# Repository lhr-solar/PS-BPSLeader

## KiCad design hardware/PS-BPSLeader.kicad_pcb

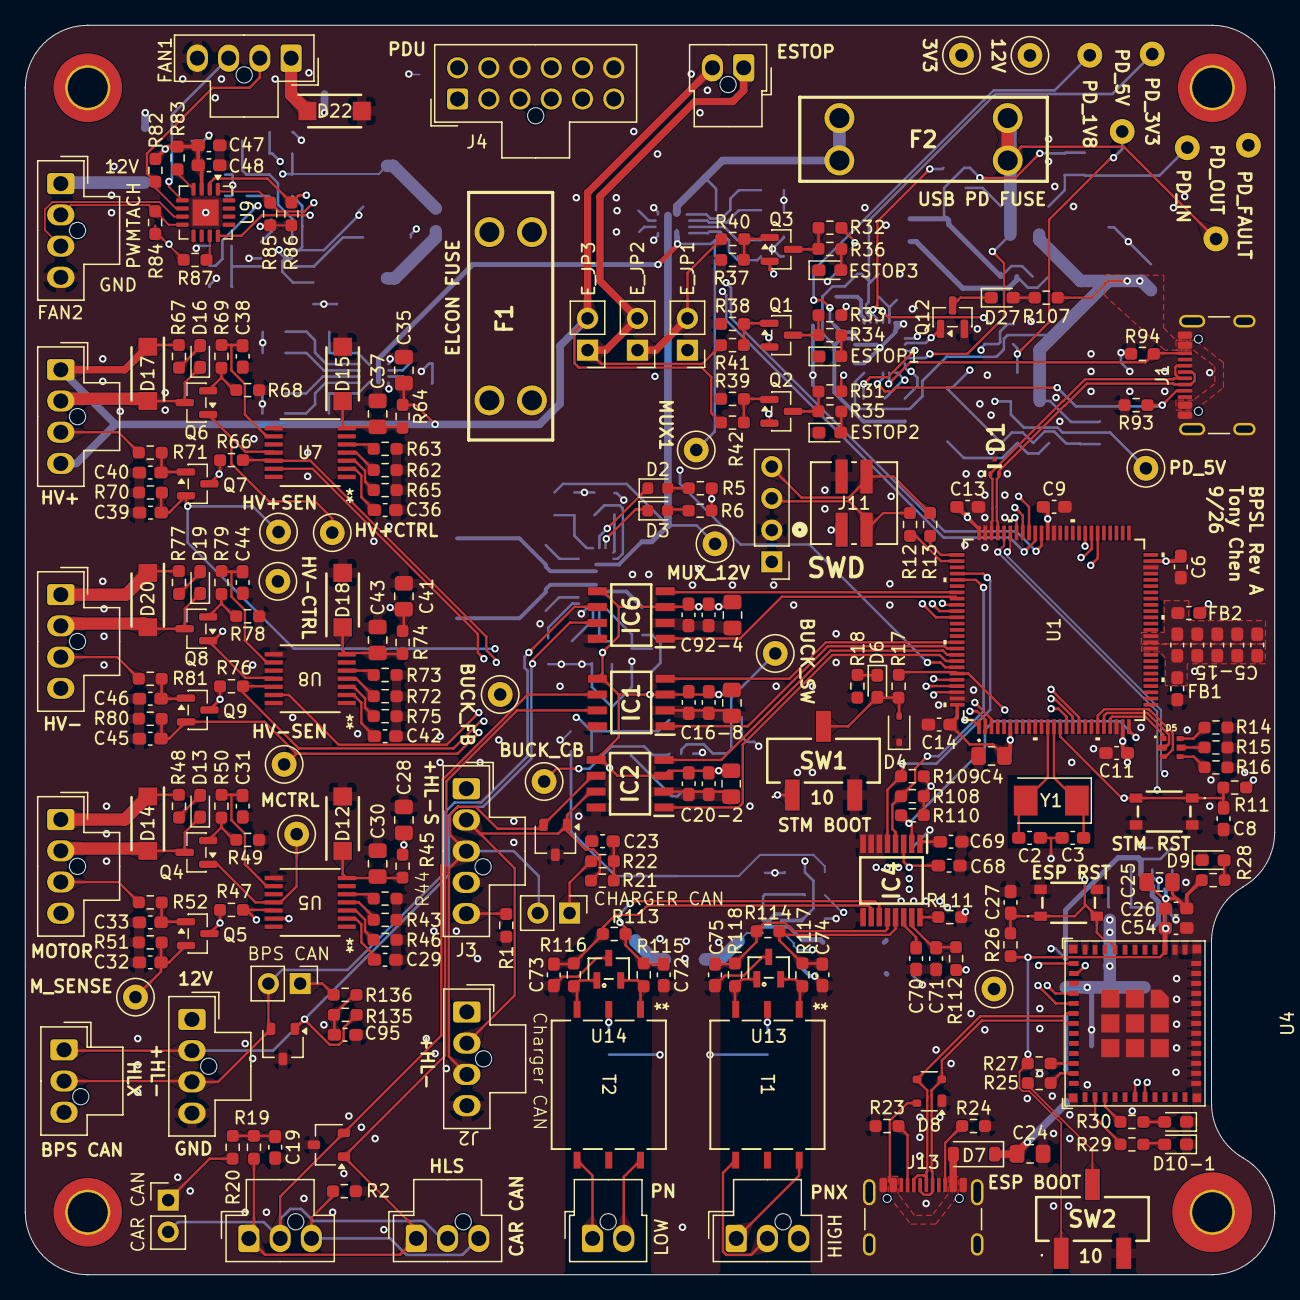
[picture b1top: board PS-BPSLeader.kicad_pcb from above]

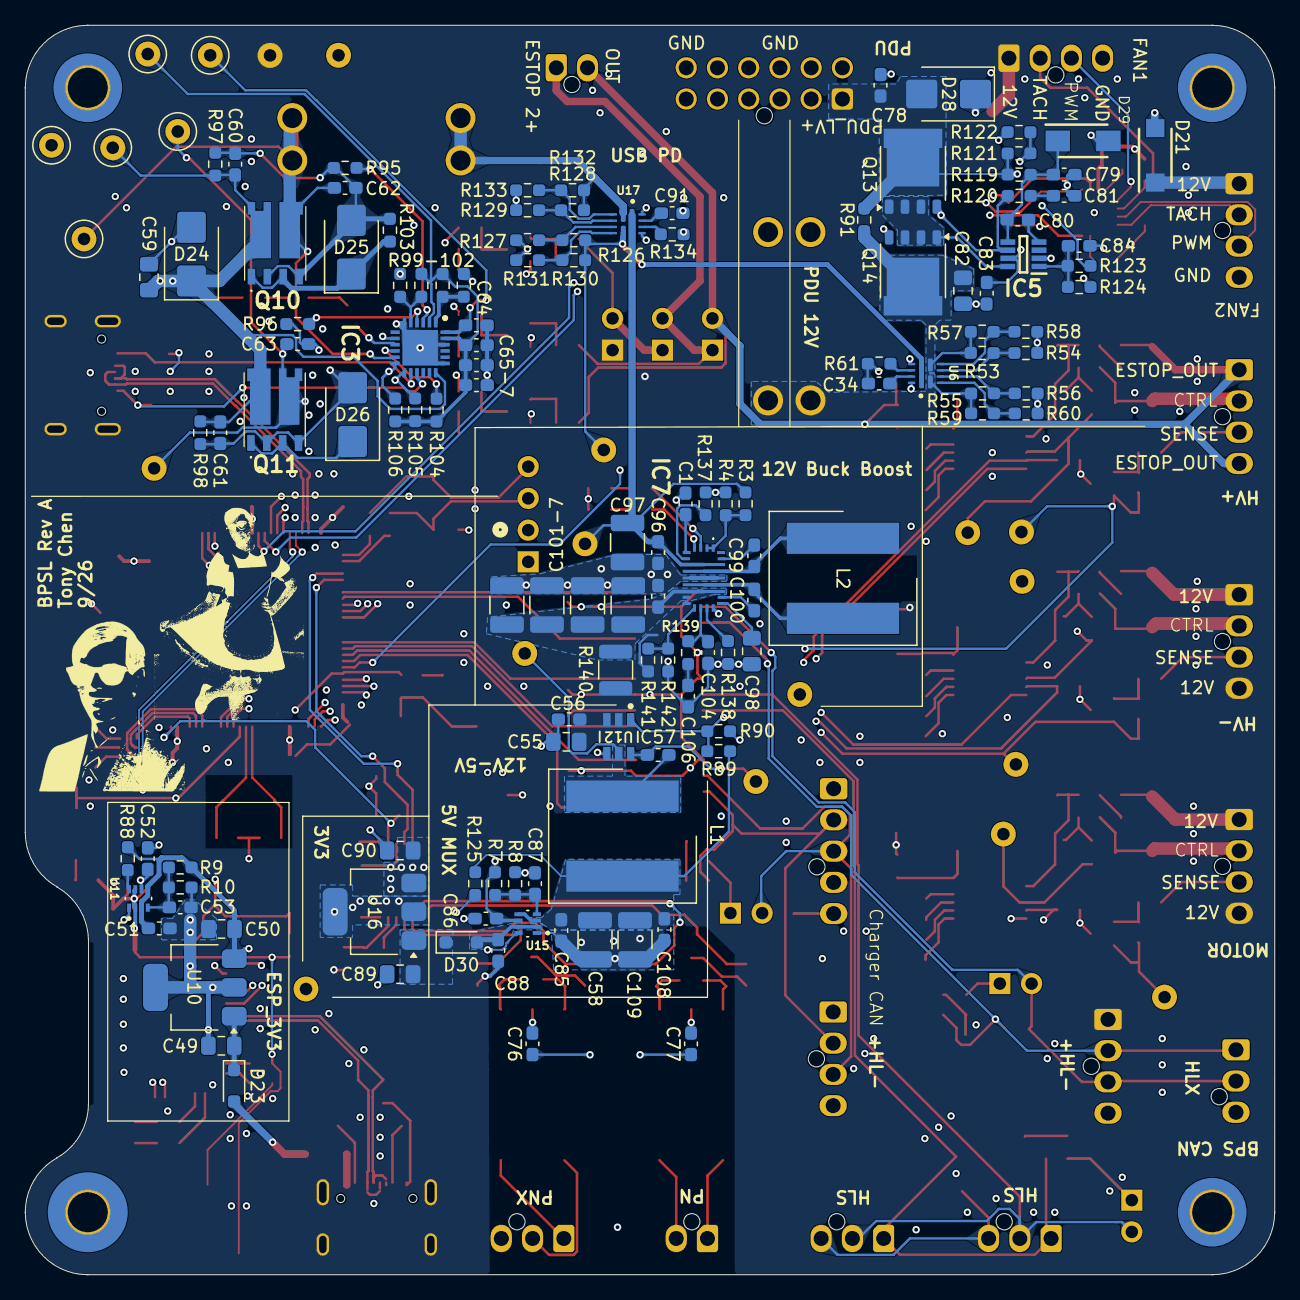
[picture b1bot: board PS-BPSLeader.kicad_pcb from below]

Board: 4 copper layers, 100.0 x 100.0 mm, 387 parts (134 on the bottom side), 230 nets.

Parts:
C1: 7.5n; C_0603_1608Metric_Pad1.08x0.95mm_HandSolder
C2, C3: 26p; C_0603_1608Metric_Pad1.08x0.95mm_HandSolder
C4, C16, C20, C49, C50, C82, C89, C90, C92: 10u; C_0805_2012Metric_Pad1.18x1.45mm_HandSolder
C5, C6, C7, C8, C9, C11, C13, C14, C15, C17, C18, C19, C21, C22, C23, C33, C40, C46, C68, C71, C78, C83, C84, C93, C94, C95, C96, C99, C100, C107: 0.1u; C_0603_1608Metric_Pad1.08x0.95mm_HandSolder
C10, C12, C29, C32, C34, C36, C39, C42, C45, C47, C48, C79, C91: 1u; C_0603_1608Metric_Pad1.08x0.95mm_HandSolder
C24, C25, C59: 10uF; C_0805_2012Metric_Pad1.18x1.45mm_HandSolder
C26, C27, C51, C52, C53, C54, C66, C67, C85, C86, C87, C88: 0.1uF; C_0603_1608Metric_Pad1.08x0.95mm_HandSolder
C28, C30, C35, C37, C41, C43, C55, C98: 4.7u; C_0805_2012Metric_Pad1.18x1.45mm_HandSolder
C31, C38, C44: 0.1n; C_0603_1608Metric_Pad1.08x0.95mm_HandSolder
C56, C57: 100n; C_0603_1608Metric_Pad1.08x0.95mm_HandSolder
C58, C97, C101, C102, C103, C105, C109: 22u; C_1210_3225Metric_Pad1.33x2.70mm_HandSolder
C60, C61, C62, C63, C64, C65: 1uF; C_0603_1608Metric_Pad1.08x0.95mm_HandSolder
C69, C70: 0.22u; C_0603_1608Metric_Pad1.08x0.95mm_HandSolder
C72, C73, C74, C75, C76, C77: 100pF; C_0603_1608Metric_Pad1.08x0.95mm_HandSolder
C80: 220n; C_0603_1608Metric_Pad1.08x0.95mm_HandSolder
C81: 10n; C_0603_1608Metric_Pad1.08x0.95mm_HandSolder
C104: 45p; C_0603_1608Metric_Pad1.08x0.95mm_HandSolder
C106: 90n; C_0603_1608Metric_Pad1.08x0.95mm_HandSolder
C108: 4.7u; C_0603_1608Metric_Pad1.08x0.95mm_HandSolder
D1: TPD2EUSB30DRTR
D2, D3: LED; LED_0603_1608Metric
D4: TVS; D_SOD-323
D5: RGB_LED
D6: LED; LED_0603_1608Metric_Pad1.05x0.95mm_HandSolder
D7: 1N5819HW-7-F; D_SOD-123
D8: SP0503BAHT; SOT-143
D9: ESP_PWR; LED_0603_1608Metric_Pad1.05x0.95mm_HandSolder
D10: ESP_LED1; LED_0603_1608Metric_Pad1.05x0.95mm_HandSolder
D11: ESP_LED2; LED_0603_1608Metric_Pad1.05x0.95mm_HandSolder
D12, D14, D15, D17, D18, D20, D21, D22: VSSAF522-M3/H; SODFL5226X100N
D13, D16, D19: Contact; LED_0603_1608Metric_Pad1.05x0.95mm_HandSolder
D23, D30: SBA130CH-AU_R1_000A1; D_SOD-323_HandSoldering
D24: SMBJ24A-E3_52; D_SMB
D25, D26: SMBJ10A-E3_52; D_SMB
D27: FAULT; LED_0603_1608Metric_Pad1.05x0.95mm_HandSolder
D28: SMBJ15CA; D_SMB
D29: SMAF4758A; SODFL5026X125N
ESTOP1, ESTOP2, ESTOP3: LED; LED_0603_1608Metric_Pad1.05x0.95mm_HandSolder
E_JP1, E_JP2, E_JP3: Jumper_2_Open; PinHeader_1x02_P2.54mm_Vertical
F1, F2: 5A; Fuse-3557-2
FAN1, FAN2: Conn_01x04; Molex_Nano-Fit_105309-xx04_1x04_P2.50mm_Vertical
FB1, FB2: FerriteBead; L_0603_1608Metric_Pad1.05x0.95mm_HandSolder
H1: MountingHole_Pad; MountingHole_3.2mm_M3_Pad_TopBottom
H2, H3, H4: MountingHole_Pad; MountingHole_3.2mm_M3_ISO14580_Pad_TopBottom
IC1, IC2, IC6: TCAN3413DR
IC3: CYPD3177-24LQXQ
IC4: BQ79600PWRQ1; SOP65P640X120-16N
IC5: LM74502DDFR
IC7: TPS552872RYQR; TPS552892QWRYQRQ1
J1, J13: USB_C_Receptacle_USB2.0_16P; USB_C_Receptacle_GCT_USB4105-xx-A_16P_TopMnt_Horizontal
J2: ELCON CAN DEBUG; Molex_Nano-Fit_105309-xx04_1x04_P2.50mm_Vertical
J3: ELCON CAN; Molex_Nano-Fit_105309-xx05_1x05_P2.50mm_Vertical
J4: Conn_02x06_Counter_Clockwise; Molex_Nano-Fit_105310-xx12_2x06_P2.50mm_Vertical
J5: CAR CAN IN; Molex_Nano-Fit_105309-xx03_1x03_P2.50mm_Vertical
J6: CAR CAN OUT; Molex_Nano-Fit_105309-xx03_1x03_P2.50mm_Vertical
J7: BPS CAN DEBUG; Molex_Nano-Fit_105309-xx04_1x04_P2.50mm_Vertical
J8: BPS CAN; Molex_Nano-Fit_105309-xx03_1x03_P2.50mm_Vertical
J9: High Side Conn; Molex_Nano-Fit_105309-xx03_1x03_P2.50mm_Vertical
J10: Low SIde Conn; Molex_Nano-Fit_105309-xx02_1x02_P2.50mm_Vertical
J11: SWD_Header; SWD_Conn
J12: SWD; PinHeader_1x04_P2.54mm_Vertical
J14: Conn_01x02; Molex_Nano-Fit_105309-xx02_1x02_P2.50mm_Vertical
J15, J16, J17: Contactor Connector; Molex_Nano-Fit_105309-xx04_1x04_P2.50mm_Vertical
JP1, JP2, JP3: TRM; PinHeader_1x02_P2.54mm_Vertical
L1: 8.2u; 74439369082
L2: 4.7u; 74439369082
LOGO1: Dr. Hallock; LHRs_LOGO
LOGO2: Dr. Hallock; Hallock_Image_Tiny
Q1, Q2, Q3: SQ2315CES-T1_GE3; SOT-23
Q4, Q5, Q6, Q7, Q8, Q9, Q12: IRLML0030; SOT-23
Q10, Q11: SI7997DP-T1-GE3
Q13, Q14: PSMN012-100YS; LFPAK56
R1, R2, R44, R63, R73, R91: 0; R_0603_1608Metric_Pad0.98x0.95mm_HandSolder
R3: 30.1k; R_0603_1608Metric_Pad0.98x0.95mm_HandSolder
R4, R54, R56, R58, R60, R127, R129, R131, R133: 5k; R_0603_1608Metric_Pad0.98x0.95mm_HandSolder
R5, R6, R14, R15, R16, R18, R28, R29, R30, R34, R35, R36, R45, R50, R64, R69, R74, R79, R95, R96, R101, R113, R114: 1k; R_0603_1608Metric_Pad0.98x0.95mm_HandSolder
R7: 16k; R_0603_1608Metric_Pad0.98x0.95mm_HandSolder
R8, R104: 4.7k; R_0603_1608Metric_Pad0.98x0.95mm_HandSolder
R9: 18k; R_0603_1608Metric_Pad0.98x0.95mm_HandSolder
R10, R11, R17, R25, R26, R27, R31, R32, R33, R37, R38, R39, R47, R51, R52, R66, R70, R71, R76, R80, R81, R82, R84, R85, R86, R88, R97, R107, R108, R109, R119, R125: 10k; R_0603_1608Metric_Pad0.98x0.95mm_HandSolder
R12, R13: 22; R_0603_1608Metric_Pad0.98x0.95mm_HandSolder
R19, R20, R21, R22, R135, R136: 60; R_0603_1608Metric_Pad0.98x0.95mm_HandSolder
R23, R24, R93, R94, R99, R100, R102: 5.1k; R_0603_1608Metric_Pad0.98x0.95mm_HandSolder
R40, R41, R42, R83, R87: 33k; R_0603_1608Metric_Pad0.98x0.95mm_HandSolder
R43, R62, R72: 66.67k; R_0603_1608Metric_Pad0.98x0.95mm_HandSolder
R46, R65, R75: 120k; R_0603_1608Metric_Pad0.98x0.95mm_HandSolder
R48, R67, R77: 4.3k; R_0603_1608Metric_Pad0.98x0.95mm_HandSolder
R49, R68, R78: 1; R_0603_1608Metric_Pad0.98x0.95mm_HandSolder
R53, R126, R132: 57.6k; R_0603_1608Metric_Pad0.98x0.95mm_HandSolder
R55: 67.3k; R_0603_1608Metric_Pad0.98x0.95mm_HandSolder
R57, R130: 26.1k; R_0603_1608Metric_Pad0.98x0.95mm_HandSolder
R59: 37.4k; R_0603_1608Metric_Pad0.98x0.95mm_HandSolder
R61, R134: 22.1k; R_0603_1608Metric_Pad0.98x0.95mm_HandSolder
R89, R110, R111, R121, R123, R128, R141: 100k; R_0603_1608Metric_Pad0.98x0.95mm_HandSolder
R90: 19.1k; R_0603_1608Metric_Pad0.98x0.95mm_HandSolder
R98, R103: 49.9k; R_0603_1608Metric_Pad0.98x0.95mm_HandSolder
R105, R106: 2.2k; R_0603_1608Metric_Pad0.98x0.95mm_HandSolder
R112: 10; R_0603_1608Metric_Pad0.98x0.95mm_HandSolder
R115, R116, R117, R118: 51; R_0603_1608Metric_Pad0.98x0.95mm_HandSolder
R120: 33; R_0603_1608Metric_Pad0.98x0.95mm_HandSolder
R122: 7.32k; R_0603_1608Metric_Pad0.98x0.95mm_HandSolder
R124: 15.8k; R_0603_1608Metric_Pad0.98x0.95mm_HandSolder
R137: 50k; R_0603_1608Metric_Pad0.98x0.95mm_HandSolder
R138: R_US; R_0603_1608Metric_Pad0.98x0.95mm_HandSolder
R139: 1.455k; R_0603_1608Metric_Pad0.98x0.95mm_HandSolder
R140: 12.5m; R_1210_3225Metric
R142: 11.1k; R_0603_1608Metric_Pad0.98x0.95mm_HandSolder
Reset1: Reset; TL3365AF180QG
SW1: SW_SPDT; BootSW
SW2: BOOT Switch; BootSW
SW3: RESET Button; TL3365AF180QG
T1, T2: HMU1228NL; HMU1228NL_PUL
TP1: PD_5V; TestPoint_Loop_D1.80mm_Drill1.0mm_Beaded
TP3: PDU_ELCON; TestPoint_Loop_D1.80mm_Drill1.0mm_Beaded
TP4: MUX_12V; TestPoint_Loop_D1.80mm_Drill1.0mm_Beaded
TP5, TP7, TP9: ctrl; TestPoint_Loop_D1.80mm_Drill1.0mm_Beaded
TP6, TP8, TP10: Sense; TestPoint_Loop_D1.80mm_Drill1.0mm_Beaded
TP11: V_in_12V; TestPoint_Loop_D1.80mm_Drill1.0mm_Beaded
TP12: CB; TestPoint_Loop_D1.80mm_Drill1.0mm_Beaded
TP13: FB; TestPoint_Loop_D1.80mm_Drill1.0mm_Beaded
TP14: SW; TestPoint_Loop_D1.80mm_Drill1.0mm_Beaded
TP15: VBUS_IN; TestPoint_Loop_D1.80mm_Drill1.0mm_Beaded
TP16: PD_VBUS_OUT; TestPoint_Loop_D1.80mm_Drill1.0mm_Beaded
TP17: PD_5V_OUT; TestPoint_Loop_D1.80mm_Drill1.0mm_Beaded
TP18: PD_1V8; TestPoint_Loop_D1.80mm_Drill1.0mm_Beaded
TP19: PD_3V3; TestPoint_Loop_D1.80mm_Drill1.0mm_Beaded
TP20: PD_FAULT; TestPoint_Loop_D1.80mm_Drill1.0mm_Beaded
TP_3.3V1, TP_3.3V2: 3.3V; TestPoint_Loop_D1.80mm_Drill1.0mm_Beaded
U1: STM32G473VETx; 100PinMCU
U2, U3, U18: CDSOT23-T24CAN
U4: ESP32-C6-MINI-1
U5, U7, U8: DRV110APWR; PW14_TEX
U6, U17: TPS2121RUXR
U9: EMC2305-1-AP-TR; Texas_RGV0016A_VQFN-16-1EP_4x4mm_P0.65mm_EP2.1x2.1mm
U10, U16: MCP1826S; SOT-223-3_TabPin2
U11, U15: TPS2117DRLR
U12: LMR51635XDDCR; DDC0006A-MFG
U13, U14: PESD5V0L2BT; SOT23_NXP
Y1: Crystal; Crystal_SMD_Abracon_ABM3-2Pin_5.0x3.2mm

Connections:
+3.3V: C4.1, C6.1, C9.1, C11.1, C13.1, C14.1, C16.1, C17.1, C18.1, C20.1, C21.1, C22.1, C47.1, C48.1, C52.1, C68.1, C90.2, C92.1, C93.1, C94.1, FB2.1, IC1.3 (VCC), IC1.5 (SHDNV_IO), IC2.3 (VCC), IC2.5 (SHDNV_IO), IC4.3 (VIO), IC6.3 (VCC), IC6.5 (SHDNV_IO), J11.1, J12.1, Q1.2 (S), Q2.2 (S), Q3.2 (S), Q5.3 (D), Q7.3 (D), Q9.3 (D), R5.1, R6.1, R11.2, R47.2, R66.2, R76.2, R82.1, R83.1, R84.1, R85.1, R86.1, R87.1, R108.1, R109.1, R110.1, SW1.1 (A), TP_3.3V2.1 (1_1), U1.6 (VBAT), U1.24 (VDD), U1.49 (VDD), U1.64 (VDD), U1.75 (VDD), U1.100 (VDD), U9.3 (VDD), U11.6 (VIN2), U16.3 (VO)
+3.3V_ESP: C25.1, C25.2, C26.1, C26.2, C54.1, R26.1, R27.2, R28.1, SW2.1 (A), U4.3 (3V3), U11.2 (VOUT), U11.7 (VOUT__1)
+5V: C88.1, D30.2 (A), U15.2 (VOUT), U15.7 (VOUT__1)
+12V: C28.1, C41.1, C55.1, C56.1, D14.1 (K), D20.1 (K), D21.1 (K), D22.1 (K), E_JP1.1 (A), FAN1.1, FAN2.1, IC7.13 (ISN), J7.1 (12V), J15.1 (Con+(12V)), J15.4 (Sense+(12V)), J17.1 (Con+(12V)), J17.4 (Sense+(12V)), R45.2, R48.2, R74.2, R77.2, R112.2, R140.2, R141.2, TP11.1 (1_1), U12.2 (EN), U12.3 (VIN)
/BMS/COMHN: C75.1, IC4.12 (COMHN), R114.2, R118.1
/BMS/COMHP: C74.1, IC4.13 (COMHP), R114.1, R117.1
/BMS/COMLN: C72.1, IC4.11 (COMLN), R113.1, R115.1
/BMS/COMLP: C73.1, IC4.10 (COMLP), R113.2, R116.1
/BMS/INH: IC4.16 (INH), R111.1
/BMS_NFAULT: IC4.2 (NFAULT), R110.2, U1.25 (PA3)
/BMS_UART_RX: IC4.4 (MOSI/RX), R108.2, U1.80 (PC11)
/BMS_UART_TX: IC4.5 (MISO/TX), R109.2, U1.79 (PC10)
/BPS_CAN_H: IC6.7 (CANH), J7.2 (CAN_H), J8.1 (CAN_H), R135.1, U18.1 (CAN_H)
/BPS_CAN_L: IC6.6 (CANL), J7.3 (CAN_L), J8.2 (CAN_L), JP3.2 (B), U18.2 (CAN_L)
/CAR_CAN_H: IC1.7 (CANH), J5.1 (CAN_H), J6.1 (CAN_H), R19.1, U2.1 (CAN_H)
/CAR_CAN_L: IC1.6 (CANL), J5.2 (CAN_L), J6.2 (CAN_L), JP1.2 (B), U2.2 (CAN_L)
/CHARGER_CAN_H: IC2.7 (CANH), J2.2 (CAN_H), J3.2 (CAN_H), R21.1, U3.1 (CAN_H)
/CHARGER_CAN_L: IC2.6 (CANL), J2.3 (CAN_L), J3.3 (CAN_L), JP2.2 (B), U3.2 (CAN_L)
/ELCON_LV+: F1.1, J2.1 (12V), J3.1 (12V)
/ESTOP_1-/2+: E_JP1.2 (B), E_JP2.1 (A), R40.2
/ESTOP_1_SENSE: R32.2, U1.84 (PD2)
/ESTOP_2-: E_JP2.2 (B), E_JP3.1 (A), J14.1, R41.2
/ESTOP_2_SENSE: R33.2, U1.85 (PD3)
/ESTOP_3_SENSE: R31.2, U1.86 (PD4)
/ESTOP_OUT: C35.1, D17.1 (K), E_JP3.2 (B), J14.2, J16.1 (Con+(12V)), J16.4 (Sense+(12V)), R42.2, R64.2, R67.2
/FAN_ALERT: U1.94 (PB7), U9.12 (*ALERT)
/FAN_SCL: R86.2, U1.65 (PC6), U9.2 (SMCLK)
/FAN_SDA: R85.2, U1.66 (PC7), U9.1 (SMDATA)
/Fan/ADDRESS_PULLUP: R83.2, U9.4 (ADDR_SEL)
/Fan/CLK_PULLUP: R87.2, U9.11 (CLK)
/Fan/FAN_1_PWM: FAN1.3, U9.5 (PWM1)
/Fan/FAN_1_TACH: FAN1.2, R82.2, U9.6 (TACH1)
/Fan/FAN_2_PWM: FAN2.3, U9.7 (PWM2)
/Fan/FAN_2_TACH: FAN2.2, R84.2, U9.8 (TACH2)
/HV+ Contactor/Econ_Sense: C38.1, R69.1, U7.9 (SENSE)
/HV+ Contactor/HV_CONTROL: D16.1 (K), D17.2 (A), J16.2 (Con-), Q6.3 (D)
/HV+_CTRL: U1.98 (PE1), U7.13 (EN)
/HV+_ECON: R66.1, U1.97 (PE0), U7.12 (STATUS)
/HV+_SENSE: C39.2, Q7.2 (S), R70.2, TP8.1 (1_1), U1.96 (PB9)
/HV- Contactor/Econ_Sense: C44.1, R79.1, U8.9 (SENSE)
/HV- Contactor/HV_CONTROL: D19.1 (K), D20.2 (A), J17.2 (Con-), Q8.3 (D)
/HV-_CTRL: U1.3 (PE4), U8.13 (EN)
/HV-_ECON: R76.1, U1.2 (PE3), U8.12 (STATUS)
/HV-_SENSE: C45.2, Q9.2 (S), R80.2, TP10.1 (1_1), U1.1 (PE2)
/MOTOR_CTRL: U1.17 (PC2), U5.13 (EN)
/MOTOR_ECON: R47.1, U1.16 (PC1), U5.12 (STATUS)
/MOTOR_SENSE: C32.2, Q5.2 (S), R51.2, TP6.1 (1_1), U1.15 (PC0)
/Motor_Contactor/Econ_Sense: C31.1, R50.1, U5.9 (SENSE)
/Motor_Contactor/HV_CONTROL: D13.1 (K), D14.2 (A), J15.2 (Con-), Q4.3 (D)
/PDU_LV+: C78.1, D28.2 (A2), J4.1, Q13.5, R91.1, R119.2, R121.1, R123.1
/Peripherals/100PinMCU/GNDA: C5.2, C7.2, C10.2, C12.2, C15.2, FB1.1, U1.35 (VSSA)
/Peripherals/100PinMCU/PA0: D5.5, U1.20 (PA0-GPIO_BLUE)
/Peripherals/100PinMCU/PA1: D5.3, U1.21 (PA1-GPIO_RED)
/Peripherals/100PinMCU/PA2: D5.1, U1.22 (PA2-GPIO_GREEN)
/Peripherals/100PinMCU/SWCLK: R12.1, U1.77 (PA14)
/Peripherals/100PinMCU/SWDIO: R13.1, U1.76 (PA13)
/Peripherals/100PinMCU/VDDA: C5.1, C7.1, C10.1, C12.1, C15.1, FB2.2, U1.36 (VREF+), U1.37 (VDDA)
/Peripherals/BPS_CAN_RX: IC6.4 (RXD), U1.82 (PD0)
/Peripherals/BPS_CAN_TX: IC6.1 (TXD), U1.83 (PD1)
/Peripherals/CAR_CAN_RX: IC1.4 (RXD), U1.90 (PB3)
/Peripherals/CAR_CAN_TX: IC1.1 (TXD), U1.91 (PB4)
/Peripherals/CHARGER_CAN_RX: IC2.4 (RXD), U1.92 (PB5)
/Peripherals/CHARGER_CAN_TX: IC2.1 (TXD), U1.93 (PB6)
/Peripherals/ESP32/+5V_LDO_IN: C24.1, D7.1 (K), D23.2 (A)
/Peripherals/ESP32/BOOT: R25.1, U4.23 (GPIO9)
/Peripherals/ESP32/LED1: R29.1, U4.26 (GPIO20)
/Peripherals/ESP32/LED2: R30.1, U4.27 (GPIO21)
/Peripherals/ESP32/USB_D+: D8.2 (K), J13.A6 (D+), J13.B6 (D+), U4.18 (GPIO13/USB_D+)
/Peripherals/ESP32/USB_D-: D8.3 (K), J13.A7 (D-), J13.B7 (D-), U4.17 (GPIO12/USB_D-)
/Peripherals/ESP32/VBUSB: D7.2 (A), D8.4 (K), J13.A4 (VBUS), J13.A9 (VBUS), J13.B4 (VBUS), J13.B9 (VBUS)
/Peripherals/ESP32_LDO/Vout: C50.2, C51.1, R9.1, R88.1, TP_3.3V1.1 (1_1), U10.3 (VO), U11.3 (VIN1), U11.5 (MODE)
/Peripherals/ESP32_Power_Mux/PR1: C53.1, R9.2, R10.1, U11.4 (PR1)
/Peripherals/ESP_GPIO3: U1.56 (PD9), U4.15 (MTCK/GPIO6/ADC1_CH6)
/Peripherals/ESP_GPIO4: U1.57 (PD10), U4.16 (MTDO/GPIO7)
/Peripherals/ESP_NRST: C27.1, R26.2, SW3.1, U1.58 (PD11), U4.8 (EN/CHIP_PU)
/Peripherals/STM_BOOT: R17.1, U1.95 (PB8-BOOT0), U4.12 (GPIO0/ADC1_CH0/XTAL_32K_P)
/Peripherals/STM_NRST: C8.1, R11.1, Reset1.1, U1.14 (PG10-NRST), U4.13 (GPIO1/ADC1_CH1/XTAL_32K_N)
/Peripherals/STM_RX: U1.71 (PA10), U4.31 (U0TXD/GPIO16)
/Peripherals/STM_TX: U1.70 (PA9), U4.30 (U0RXD/GPIO17)
/Power/5V_BUCK: C58.1, C85.1, C108.1, C109.1, L1.2, R89.1, R125.1, U15.3 (VIN1), U15.5 (MODE)
/Power/12VBuck/CB: C57.1, TP12.1 (1_1), U12.6 (CB)
/Power/12VBuck/FB: R89.2, R90.1, TP13.1 (1_1), U12.1 (FB)
/Power/12VBuck/SW: C57.2, L1.1, TP14.1 (1_1), U12.5 (SW)
/Power/12V_CC: D3.1 (K), IC7.4 (~CC)
/Power/12V_DITH: C1.1, IC7.5 (DITH/SYNC)
/Power/12V_PG: D2.1 (K), IC7.3 (PG)
/Power/EN: IC7.1 (EN/UVLO), IC7.2 (MODE), R3.2, R4.1
/Power/MUX_12V: C96.1, C97.1, IC7.7 (VIN), R3.1, TP4.1 (1_1), U17.1 (OUT), U17.8 (OUT)
/Power/PDU_12V: C82.1, Q14.5, R53.1, R57.1, R91.2, U6.7 (IN1)
/Power/PD_5V_OUT: C63.1, C86.1, Q11.5 (D2), Q11.6 (D2), Q11.10 (D2), Q11.12 (D2), R7.1, TP1.1 (1_1), TP17.1 (1_1), U15.6 (VIN2)
/Power/PowerProtection/EN/UVLO: C84.2, IC5.1 (EN/UVLO), R123.2, R124.2
/Power/PowerProtection/OV: C83.2, IC5.7 (OV), R121.2, R122.1
/Power/PowerProtection/gate: IC5.6 (GATE), Q13.4, Q14.4, R120.2
/Power/PowerProtection/source: IC5.8 (SRC), Q13.1, Q13.2, Q13.3, Q14.1, Q14.2, Q14.3
/Power/Power_5VMux/PR1: C87.1, R7.2, R8.1, U15.4 (PR1)
/Power/Power_Mux_PD/CP2: R132.2, R133.1, U17.3 (CP2)
/Power/Power_Mux_PD/OV1: R126.2, R127.1, U17.5 (OV1)
/Power/Power_Mux_PD/OV2: R128.2, R129.1, U17.4 (OV2)
/Power/Power_Mux_PD/PRI: R130.2, R131.1, U17.6 (PR1)
/Power/Power_Mux_PD/Vin1: R126.1, R130.1, TP3.1 (1_1), U6.1 (OUT), U6.8 (OUT), U17.7 (IN1)
/Power/Power_Mux_PD/Vin2: F2.2, R128.1, R132.1, U17.2 (IN2)
/Power/Power_Mux_PDU_ELCON/CP2: R59.2, R60.1, U6.3 (CP2)
/Power/Power_Mux_PDU_ELCON/OV1: R53.2, R54.1, U6.5 (OV1)
/Power/Power_Mux_PDU_ELCON/OV2: R55.2, R56.1, U6.4 (OV2)
/Power/Power_Mux_PDU_ELCON/PRI: R57.2, R58.1, U6.6 (PR1)
/Power/Power_Mux_PDU_ELCON/Vin2: F1.2, R55.1, R59.1, U6.2 (IN2)
/Power/Power_USB_PD/ISINK_COARSE: IC3.5 (ISNK_COARSE), R100.2, R102.1
/Power/Power_USB_PD/PD_1V8: C64.2, IC3.24 (VCCD), TP18.1 (1_1)
/Power/Power_USB_PD/PD_3V3: C65.1, C66.1, C67.1, IC3.2 (VBUS_MAX), IC3.23 (VDDD), R99.1, R100.1, R104.1, R105.1, R106.1, TP19.1 (1_1)
/Power/Power_USB_PD/PD_FAULT: IC3.9 (FAULT), Q12.1 (G), TP20.1 (1_1)
/Power/Power_USB_PD/SAFE_PWR_EN: IC3.4 (SAFE_PWR_EN), R96.2
/Power/Power_USB_PD/VBUS_FET_EN: IC3.3 (VBUS_FET_EN), R95.2
/Power/Power_USB_PD/VBUS_MIN: IC3.1 (VBUS_MIN), R99.2, R101.1
/Power/USB_PD_OUT: C62.1, F2.1, IC3.11 (VDC_OUT), Q10.5 (D2), Q10.6 (D2), Q10.10 (D2), Q10.12 (D2), TP16.1 (1_1)
/SHIELD: J5.3 (SHIELD), J6.3 (SHIELD), R2.1
/USB_CC1: IC3.15 (CC1), J1.A5 (CC1), R93.1
/USB_CC2: IC3.14 (CC2), J1.B5 (CC2), R94.1
/USB_D+: D1.1 (D+), J1.A6 (D+), J1.B6 (D+), U1.73 (PA12)
/USB_D-: D1.2 (D-), J1.A7 (D-), J1.B7 (D-), U1.72 (PA11)
/USB_GPIO: IC3.8 (GPIO_1), U1.69 (PA8)
/USB_SCL: IC3.13 (HPI_SCL), R105.2, U1.67 (PC8)
/USB_SDA: IC3.12 (HPI_SDA), R106.2, U1.68 (PC9)
/USB_VBUS_IN: C59.1, C60.1, C61.1, D24.1 (K), IC3.18 (VBUS_IN), J1.A4 (VBUS), J1.A9 (VBUS), J1.B4 (VBUS), J1.B9 (VBUS), Q10.7 (D1), Q10.8 (D1), Q10.9 (D1), Q10.11 (D1), Q11.7 (D1), Q11.8 (D1), Q11.9 (D1), Q11.11 (D1), R97.2, R98.2, R107.1, TP15.1 (1_1)
/isolatedCOMHN: J9.2, T1.4 (TX-)
/isolatedCOMHP: J9.1, T1.6 (TX+)
/isolatedCOMLN: J10.2, T2.6 (TX+)
/isolatedCOMLP: J10.1, T2.4 (TX-)
GND: C1.2, C2.1, C3.1, C4.2, C6.2, C8.2, C9.2, C11.2, C13.2, C14.2, C16.2, C17.2, C18.2, C19.2, C20.2, C21.2, C22.2, C23.2, C24.2, C27.2, C28.2, C29.2, C30.2, C31.2, C32.1, C33.1, C34.2, C35.2, C36.2, C37.2, C38.2, C39.1, C40.1, C41.2, C42.2, C43.2, C44.2, C45.1, C46.1, C47.2, C48.2, C49.1, C50.1, C51.2, C52.2, C53.2, C54.2, C55.2, C56.2, C58.2, C59.2, C64.1, C65.2, C66.2, C67.2, C68.2, C69.2, C70.2, C71.2, C72.2, C73.2, C74.2, C75.2, C76.1, C77.1, C78.2, C79.1, C81.2, C82.2, C83.1, C84.1, C85.2, C86.2, C87.2, C88.2, C89.1, C90.1, C91.2, C92.2, C93.2, C94.2, C95.2, C96.2, C97.2, C98.2, C101.2, C102.2, C103.2, C104.2, C105.2, C106.2, C107.2, C108.2, C109.2, D1.3 (GND), D4.1 (A1), D8.1 (A), D9.1 (K), D10.1 (K), D11.1 (K), D12.2 (A), D15.2 (A), D18.2 (A), D21.2 (A), D22.2 (A), D24.2 (A), D28.1 (A1), D29.2 (A), ESTOP1.1 (K), ESTOP2.1 (K), ESTOP3.1 (K), FAN1.4, FAN2.4, FB1.2, IC1.2 (GND), IC1.8 (STB), IC2.2 (GND), IC2.8 (STB), IC3.6 (ISNK_FINE), IC3.19 (GND_1), IC3.22 (GND_2), IC3.25 (GND_3), IC4.6 (SCLK), IC4.7 (NCS), IC4.8 (NUART/SPI_(SPI_RDY)), IC4.9 (GND), IC5.2 (GND), IC6.2 (GND), IC6.8 (STB), IC7.9 (PGND_1), IC7.17 (AGND), IC7.22 (PGND_2), IC7.23 (PGND_3), J1.A1 (GND), J1.A12 (GND), J1.B1 (GND), J1.B12 (GND), J1.S1 (SHIELD), J1.S2 (Shield), J1.S3 (Shield), J1.S4 (Shield), J2.4 (GND), J3.4 (GND), J4.9, J4.12, J7.4 (GND), J11.2, J12.2, J13.A1 (GND), J13.A12 (GND), J13.B1 (GND), J13.B12 (GND), J13.S1 (SHIELD), J13.S2 (Shield), J13.S3 (Shield), J13.S4 (Shield), Q12.2 (S), R1.2, R2.2, R4.2, R8.2, R10.2, R14.2, R15.2, R16.2, R18.2, R23.2, R24.2, R37.1, R38.1, R39.1, R43.1, R44.1, R46.1, R49.1, R51.1, R54.2, R56.2, R58.2, R60.2, R61.2, R62.1, R63.1, R65.1, R68.1, R70.1, R72.1, R73.1, R75.1, R78.1, R80.1, R90.2, R93.2, R94.2, R101.2, R102.2, R111.2, R122.2, R124.1, R127.2, R129.2, R131.2, R133.2, R134.2, R137.1, R138.1, R142.2, Reset1.2, SW1.3 (C), SW2.3 (C), SW3.2, U1.23 (VSS), U1.48 (VSS), U1.63 (VSS), U1.74 (VSS), U1.99 (VSS), U2.3 (GND), U3.3 (GND), U4.1 (GND), U4.2 (GND), U4.11 (GND), U4.14 (GND), U4.36 (GND), U4.37 (GND), U4.38 (GND), U4.39 (GND), U4.40 (GND), U4.41 (GND), U4.42 (GND), U4.43 (GND), U4.44 (GND), U4.45 (GND), U4.46 (GND), U4.47 (GND), U4.48 (GND), U4.49 (GND), U4.50 (GND), U4.51 (GND), U4.52 (GND), U4.53 (GND), U5.8 (GND), U6.9 (ST), U6.12 (GND), U7.8 (GND), U8.8 (GND), U9.17 (EPAD), U10.2 (GND), U11.1 (GND), U12.4 (GND), U13.3, U14.3, U15.1 (GND), U16.2 (GND), U17.9 (ST), U17.12 (GND), U18.3 (GND)
unnamed: C19.1, R19.2, R20.1
unnamed: C23.1, R21.2, R22.1
unnamed: C81.1, R120.1
unnamed: C95.1, R135.2, R136.1
unnamed: C106.1, R139.2
unnamed: D2.2 (A), R5.2
unnamed: D3.2 (A), R6.2
unnamed: D4.2 (A2), D6.2 (A), R17.2, SW1.2 (B)
unnamed: D5.2, R14.1
unnamed: D5.4, R15.1
unnamed: D5.6, R16.1
unnamed: D6.1 (K), R18.1
unnamed: D9.2 (A), R28.2
unnamed: D10.2 (A), R29.2
unnamed: D11.2 (A), R30.2
unnamed: C30.1, D12.1 (K), R45.1, U5.7 (VIN)
unnamed: D13.2 (A), R48.1
unnamed: C37.1, D15.1 (K), R64.1, U7.7 (VIN)
unnamed: D16.2 (A), R67.1
unnamed: C43.1, D18.1 (K), R74.1, U8.7 (VIN)
unnamed: D19.2 (A), R77.1
unnamed: C49.2, D23.1 (K), U10.1 (VI)
unnamed: C60.2, C62.2, D25.2 (A), Q10.2 (G1), Q10.4 (G2), R95.1, R97.1, R103.1
unnamed: D25.1 (K), Q10.1 (S1), Q10.3 (S2), R103.2
unnamed: C61.2, C63.2, D26.2 (A), Q11.2 (G1), Q11.4 (G2), R96.1, R98.1
unnamed: D26.1 (K), Q11.1 (S1), Q11.3 (S2)
unnamed: D27.2 (A), R107.2
unnamed: D27.1 (K), Q12.3 (D)
unnamed: C79.2, C80.1, D29.1 (K), IC5.5 (VS), R119.1
unnamed: C89.2, D30.1 (K), U16.1 (VI)
unnamed: ESTOP1.2 (A), R34.2
unnamed: ESTOP2.2 (A), R35.2
unnamed: ESTOP3.2 (A), R36.2
unnamed: IC3.10 (FLIP), R104.2
unnamed: C71.1, IC4.15 (BAT), R112.1
unnamed: C70.1, IC4.14 (CVDD)
unnamed: C69.1, IC4.1 (DVDD)
unnamed: C80.2, IC5.4 (VCAP)
unnamed: C99.1, IC7.20 (BOOT1)
unnamed: C100.2, IC7.19 (BOOT2)
unnamed: IC7.16 (CDC), R138.2
unnamed: C104.1, IC7.15 (COMP), R139.1
unnamed: IC7.14 (FB), R141.1, R142.1
unnamed: IC7.6 (FSW), R137.2
unnamed: C101.1, C102.1, C103.1, C105.1, C107.1, IC7.11 (VOUT), IC7.12 (ISP), R140.1
unnamed: C99.2, IC7.8 (SW1), L2.1
unnamed: C100.1, IC7.10 (SW2), L2.2
unnamed: C98.1, IC7.18 (VCC)
unnamed: J3.5 (SHIELD), R1.1
unnamed: J11.3, J12.3, R12.2
unnamed: J11.4, J12.4, R13.2
unnamed: J13.A5 (CC1), R23.1
unnamed: J13.B5 (CC2), R24.1
unnamed: J15.3 (Sense-), R52.1
unnamed: J16.3 (Sense-), R71.1
unnamed: J17.3 (Sense-), R81.1
unnamed: JP1.1 (A), R20.2
unnamed: JP2.1 (A), R22.2
unnamed: JP3.1 (A), R136.2
unnamed: Q1.3 (D), R33.1, R34.1
unnamed: Q1.1 (G), R38.2, R41.1
unnamed: Q2.3 (D), R31.1, R35.1
unnamed: Q2.1 (G), R39.2, R42.1
unnamed: Q3.3 (D), R32.1, R36.1
unnamed: Q3.1 (G), R37.2, R40.1
unnamed: Q4.1 (G), TP5.1 (1_1), U5.11 (OUT)
unnamed: Q4.2 (S), R49.2, R50.2
unnamed: C33.2, Q5.1 (G), R52.2
unnamed: Q6.1 (G), TP7.1 (1_1), U7.11 (OUT)
unnamed: Q6.2 (S), R68.2, R69.2
unnamed: C40.2, Q7.1 (G), R71.2
unnamed: Q8.1 (G), TP9.1 (1_1), U8.11 (OUT)
unnamed: Q8.2 (S), R78.2, R79.2
unnamed: C46.2, Q9.1 (G), R81.2
unnamed: R25.2, SW2.2 (B)
unnamed: C76.2, T1.2 (TCT)
unnamed: R117.2, T1.1 (TD+), U13.2
unnamed: R118.2, T1.3 (TD-), U13.1
unnamed: C77.2, T2.2 (TCT)
unnamed: R115.2, T2.1 (TD+), U14.2
unnamed: R116.2, T2.3 (TD-), U14.1
unnamed: C2.2, U1.12 (PF0-OSC_IN), Y1.2
unnamed: C3.2, U1.13 (PF1-OSC_OUT), Y1.1
unnamed: R27.1, U4.22 (GPIO8)
unnamed: R43.2, U5.4 (HOLD)
unnamed: C29.1, U5.2 (KEEP)
unnamed: R44.2, U5.5 (OSC)
unnamed: R46.2, U5.3 (PEAK)
unnamed: R61.1, U6.10 (ILIM)
unnamed: C34.1, U6.11 (SS)
unnamed: R62.2, U7.4 (HOLD)
unnamed: C36.1, U7.2 (KEEP)
unnamed: R63.2, U7.5 (OSC)
unnamed: R65.2, U7.3 (PEAK)
unnamed: R72.2, U8.4 (HOLD)
unnamed: C42.1, U8.2 (KEEP)
unnamed: R73.2, U8.5 (OSC)
unnamed: R75.2, U8.3 (PEAK)
unnamed: R88.2, U11.8 (ST)
unnamed: R125.2, U15.8 (ST)
unnamed: R134.1, U17.10 (ILIM)
unnamed: C91.1, U17.11 (SS)

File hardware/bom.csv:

Designator,Footprint,Quantity,Value,LCSC Part #,Mouser Part #
C1,0603,1,7.5n,C907758,GRM1885C1H752JA01J
"C10, C12, C32, C39, C45, C47, C48, C79",0603,8,1u,C15849,CC0603KRX7R9BB105
"C100, C107, C19, C23, C68, C71, C83, C84, C95, C96, C99",0603,11,0.1u,C1591,MLASH168SB7104KTNA01
"C101, C102, C103, C105, C97",1206,5,22u,C5448976,GGM31CD70J226KE02L
C104,0603,1,45p,C105622,CL10C470JB8NNNC
C106,0603,1,90n,C282075,0603N910J500CT
"C11, C13, C14, C15, C17, C18, C21, C22, C33, C40, C46, C5, C6, C7, C78, C8, C9, C93, C94",0603,19,0.1u,C14663,MLASH168SB7104KTNA01
"C16, C20, C4, C49, C50, C82, C89, C90, C92",0805,9,10u,C440198,GRM21BR61H106KE43L
"C2, C3",0603,2,26p,C92670,CC0603JRNPO9BN270
"C24, C25, C59",0805,3,10uF,C440198,GRM21BR61H106KE43L
"C26, C27, C66, C67",0603,4,0.1uF,C14663,CL10B104KB8NNNC
"C28, C30, C35, C37, C41, C43, C98",0805,7,4.7u,C105911,C0805B475K050T
"C29, C34, C36, C42, C91",0603,5,1u,C15849,CC0603KRX7R9BB105
"C31, C38, C44",0603,3,0.1n,C14665,KGM15AR71C101KT
"C51, C52, C53, C54, C85, C86, C87, C88",0603,8,0.1uF,C1591,MLASH168SB7104KTNA01
C55,0805,1,4.7u,C6962403,C0805B475K050T
"C56, C57",0603,2,100n,C6666325,MLASH168SB7104KTNA01
C58,1210,1,47u,C7432791,TMK325ABJ476MM-P
"C60, C61, C62, C63, C64, C65",0603,6,1uF,C15849,CC0603KRX7R9BB105
"C69, C70",0603,2,0.22u,C107083,CC0603KRX7R9BB224
"C72, C73, C74, C75, C76, C77",0603,6,100pF,C14665,KGM15AR71C101KT
C80,0603,1,220n,C344195,CC0603KRX7R9BB224
C81,0603,1,10n,C100042,CC0603KRX7R9BB103
D1,TPD2EUSB30DRTR,1,TPD2EUSB30DRTR,C97502,TPD2EUSB30DRTR
D10,0603,1,ESP_LED1,C7371904,
D11,0603,1,ESP_LED2,C7371904,
"D12, D14, D15, D17, D18, D20, D21, D22",SODFL5226X100N,8,VSSAF522-M3/H,C6326606,VSSAF522-M3/H
"D13, D16, D19",0603,3,Contact,C84263,
"D2, D3, D6",0603,3,LED,C125103,
"D23, D30",D_SOD-323_HandSoldering,2,SBA130CH-AU_R1_000A1,C191023,SBA130CH-AU_R1_000A1 
D24,D_SMB,1,SMBJ24A-E3_52,C435936,SMBJ24A-E3_52
"D25, D26",D_SMB,2,SMBJ10A-E3_52,C1973203,SMBJ10A-E3_52
D27,0603,1,FAULT,C84263,
D28,D_SMB,1,SMBJ15CA,C669039,SMBJ15CA
D29,SODFL5026X125N,1,SMAF4758A,C183490,SMAF4758A-TP
D4,D_SOD-323,1,TVS,C725495,ESDLC5V0D3B-TP 
D5,RGB_LED,1,RGB_LED,C264519,
D7,D_SOD-123,1,1N5819HW-7-F,C82544,1N5819HW-7-F
D8,SOT-143,1,SP0503BAHT,C7074,SP0503BAHT
D9,0603,1,ESP_PWR,C7371904,
"ESTOP1, ESTOP2, ESTOP3",0603,3,LED,C84263,
"F1, F2",Fuse-3557-2,2,5A,C3205238,3557-20
"FAN1, FAN2",Molex_Nano-Fit_105309-xx04_1x04_P2.50mm_Vertical,2,Conn_01x04,,105309-1104
"FB1, FB2",0603,2,FerriteBead,C2649096,MFBW1V2012-121-R
"IC1, IC2, IC6",TCAN3413DR,3,TCAN3413DR,C22433320,TCAN3413DR
IC3,CYPD3177-24LQXQ,1,CYPD3177-24LQXQ,C2959321,CYPD3177-24LQXQ
IC4,SOP65P640X120-16N,1,BQ79600PWRQ1,C2869947,BQ79600PWRQ1
IC5,LM74502DDFR,1,LM74502DDFR,C3236215,LM74502DDFR
IC7,TPS552892QWRYQRQ1,1,TPS552872RYQR,TPS552872RYQR,TPS552872RYQR
J1,USB_C_Receptacle_GCT_USB4105-xx-A_16P_TopMnt_Horizontal,1,USB_C_Receptacle_USB2.0_16P,,USB4105-GF-A
J10,Molex_Nano-Fit_105309-xx02_1x02_P2.50mm_Vertical,1,Low SIde Conn,,105313-1102
J11,SWD_Conn,1,SWD_Header,C17492485,87832-0406
J13,USB_C_Receptacle_GCT_USB4105-xx-A_16P_TopMnt_Horizontal,1,USB_C_Receptacle_USB2.0_16P,C3020560,USB4105-GF-A
J14,Molex_Nano-Fit_105309-xx02_1x02_P2.50mm_Vertical,1,Conn_01x02,,105309-1102
"J15, J16, J17",Molex_Nano-Fit_105309-xx04_1x04_P2.50mm_Vertical,3,Contactor Connector,,105309-1104
J2,Molex_Nano-Fit_105309-xx04_1x04_P2.50mm_Vertical,1,ELCON CAN DEBUG,,105309-1104
J3,Molex_Nano-Fit_105309-xx05_1x05_P2.50mm_Vertical,1,ELCON CAN,,105309-1105
J4,Molex_Nano-Fit_105310-xx12_2x06_P2.50mm_Vertical,1,Conn_02x06_Counter_Clockwise,,105310-1112
J5,Molex_Nano-Fit_105309-xx03_1x03_P2.50mm_Vertical,1,CAR CAN IN,,105309-1103
J6,Molex_Nano-Fit_105309-xx03_1x03_P2.50mm_Vertical,1,CAR CAN OUT,,105309-1103
J7,Molex_Nano-Fit_105309-xx04_1x04_P2.50mm_Vertical,1,BPS CAN DEBUG,,105309-1104
J8,Molex_Nano-Fit_105309-xx03_1x03_P2.50mm_Vertical,1,BPS CAN,,105309-1103
J9,Molex_Nano-Fit_105309-xx03_1x03_P2.50mm_Vertical,1,High Side Conn,,105309-1103
L1,74439369082,1,8.2u,,74439369082
L2,74439369047,1,4.7u,,74439369047
"Q1, Q2, Q3",SOT-23,3,SQ2315CES-T1_GE3,C10487,SQ2315CES-T1_GE3
"Q10, Q11",SI7997DP-T1-GE3,2,SI7997DP-T1-GE3,C913432,SI7997DP-T1-GE3
"Q12, Q4, Q5, Q6, Q7, Q8, Q9",SOT-23,7,IRLML0030,C67272,IRLML0030
"Q13, Q14",LFPAK56,2,PSMN012-100YS,C20443035,PSMN012-100YS
"R1, R44, R63, R73",0603,4,0,C844719,CRCW06030000Z0EAHP
"R10, R108, R109, R125, R47, R51, R52, R66, R70, R71, R76, R80, R81, R85, R86, R88",0603,16,10k,C25804,CR0603-FX-1002ELF
"R100, R102, R23, R24, R93, R94, R99",0603,7,5.1k,C23186,CRCW06035K10FKEBC
"R101, R14, R15, R16, R18, R28, R29, R30, R95, R96",0603,10,1k,C21190,CRCW06031K00FKEI 
"R103, R98",0603,2,49.9k,C4117233,CR0603-FX-4992ELF
R104,0603,1,4.7k,C23162,RC0603FR-134K7L
"R105, R106",0603,2,2.2k,C844925,CRCW06032K20FKEAC
R107,0603,1,10k,C25804,CR0603-FX-1002ELF
"R11, R119, R17, R25, R26, R27, R31, R32, R33, R37, R38, R39, R82, R84, R97",0603,15,10k,C25804,CR0603-FX-1002ELF
"R110, R111, R128, R141",0603,4,100k,C25803,CRCW0603100KFKEE 
R112,0603,1,10,C22859,CRCW060310R0FKEA
"R113, R114, R45, R5, R50, R6, R64, R69, R74, R79",0603,10,1k,C21190,CRCW06031K00FKEI 
"R115, R116, R117, R118",0603,4,51,C2907050,CR0603-JW-510ELF
"R12, R13",0603,2,22,C2930077,RC0603FR-7W22RL
R120,0603,1,33,C844927,RT0603BRD0733RL
R121,0603,1,100k,C25803,CRCW0603100KFKEE 
R122,0603,1,7.32k,C2933256,CRCW06037K32FKEAC
R123,0603,1,100k,C25803,CRCW0603100KFKEE 
R124,0603,1,15.8k,C2960716,AC0603FR-0715K8L
"R126, R132, R53",0603,3,57.6k,C2933240,CR0603-FX-5762ELF
"R127, R129, R131, R133, R4, R54, R56, R58, R60",0603,9,5k,C862232,RT0603BRE075KL
"R130, R57",0603,2,26.1k,C321818,CR0603-FX-2612ELF
"R134, R61",0603,2,22.1k,C2960862,RT0603FRE0722K1L
"R135, R136, R19, R20, R21, R22",0603,6,60,C166918,RT0603FRE0760R4L
R137,0603,1,50k,C4117233,CR0603-FX-4992ELF
R139,0603,1,1.455k,C22841,CR0603-FX-1431ELF
R140,1210,1,12.5m,C7467372,ERJ-8CWJR013V
R142,0603,1,11.1k,C1854558,RNCF0603BTE11K1
R3,0603,1,30.1k,C2930090,RC0603FR-1330K1L
"R34, R35, R36",0603,3,1k,C21190,CRCW06031K00FKEI 
"R40, R41, R42, R83, R87",0603,5,33k,C4216,CRCW060333K0FKEA
"R43, R62, R72",0603,3,66.67k,C2933250,AC0603FR-0766K5L
"R46, R65, R75",0603,3,120k,C2906987,RK73B1JTTD124J
"R48, R67, R77",0603,3,4.3k,C54920924,CR0603-FX-4301ELF
"R49, R68, R78",0603,3,1,C2907004,RK73B1JTTD1R0J
R55,0603,1,67.3k,C861518,RT0603BRD0767K3L
R59,0603,1,37.4k,C23033,RC0603FR-0737K4L
R7,0603,1,16k,C4210,CRCW060316K0FKEA
R8,0603,1,4.7k,C23162,RC0603FR-134K7L
R89,0603,1,100k,C25803,CRCW0603100KFKEE 
R9,0603,1,18k,C2907001,AC0603FR-0718KL
R90,0603,1,19.1k,C844132,CRCW060319K1FKEA
RESET1,TL3365AF180QG,1,Reset,C2886926,TL3365AF180QG
SW1,BootSW,1,SW_SPDT,-,4.50406E+11
SW2,BootSW,1,BOOT Switch,,4.50406E+11
SW3,TL3365AF180QG,1,RESET Button,C2886926,TL3365AF180QG
"T1, T2",HMU1228NL_PUL,2,HMU1228NL,C6631737,HMU1228NL
U1,100PinMCU,1,STM32G473VETx,C730122,STM32G473VETx
"U10, U16",SOT-223-3_TabPin2,2,MCP1826S,C126055,MCP1826S
"U11, U15",TPS2117DRLR,2,TPS2117DRLR,C22399676,TPS2117DRLR
U12,DDC0006A-MFG,1,LMR51635XDDCR,C42432812,LMR51635XDDCR
"U13, U14",SOT23_NXP,2,PESD5V0L2BT,C12324,PESD5V0L2BT
"U17, U6",TPS2121RUXR,2,TPS2121RUXR,C485916,TPS2121RUXR
"U18, U2, U3",CDSOT23-T24CAN,3,CDSOT23-T24CAN,C2959841,CDSOT23-T24CAN
U4,ESP32-C6-MINI-1,1,ESP32-C6-MINI-1,C5736265,ESP32-C6-MINI-1
"U5, U7, U8",PW14_TEX,3,DRV110APWR,C2653796,DRV110APWR
U9,QFN-16-1EP_1.8x2.6mm_P0.4mm_EP0.7x1.5mm,1,EMC2305-1-AP-TR,C621415,EMC2305-1-AP-TR
Y1,Crystal_SMD_Abracon_ABM3-2Pin_5.0x3.2mm,1,Crystal,C144380,ABM3-8.000MHZ-D2Y-T

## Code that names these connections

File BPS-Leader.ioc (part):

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Mcu.Name=STM32G473V(B-C-E)Tx
Mcu.Package=LQFP100
Mcu.UserName=STM32G473VETx
PA0.Signal=GPIO_Output
PA1.Signal=GPIO_Output
PA10.Mode=Asynchronous
PA10.Signal=USART1_RX
PA11.Mode=Device
PA11.Signal=USB_DM
PA12.Mode=Device
PA12.Signal=USB_DP
PA13.Mode=Serial_Wire
PA13.Signal=SYS_JTMS-SWDIO
PA14.Mode=Serial_Wire
PA14.Signal=SYS_JTCK-SWCLK
PA2.Signal=GPIO_Output
PA3.Signal=GPIO_Input
PA9.Mode=Asynchronous
PA9.Signal=USART1_TX
PB12.Mode=NSS_Signal_Hard_Output
PB12.Signal=SPI2_NSS
PB13.Mode=Full_Duplex_Master
PB13.Signal=SPI2_SCK
PB14.Mode=Full_Duplex_Master
PB14.Signal=SPI2_MISO
PB15.Mode=Full_Duplex_Master
PB15.Signal=SPI2_MOSI
PB3.Mode=FDCAN_Activate
PB3.Signal=FDCAN3_RX
PB4.Mode=FDCAN_Activate
PB4.Signal=FDCAN3_TX
PB5.Mode=FDCAN_Activate
PB5.Signal=FDCAN2_RX
PB6.Mode=FDCAN_Activate
PB6.Signal=FDCAN2_TX
PB7.Signal=GPIO_Input
PB9.Signal=GPIO_Input
PC0.Signal=GPIO_Input
PC1.Signal=GPIO_Input
PC10.Mode=Asynchronous
PC10.Signal=USART3_TX
PC11.Mode=Asynchronous
PC11.Signal=USART3_RX
PC2.Signal=GPIO_Output
PC6.Mode=I2C
PC6.Signal=I2C4_SCL
PC7.Mode=I2C
PC7.Signal=I2C4_SDA
PD0.Mode=FDCAN_Activate
PD0.Signal=FDCAN1_RX
PD1.Mode=FDCAN_Activate
PD1.Signal=FDCAN1_TX
PD10.Signal=GPIO_Input
PD11.Signal=GPIO_Input
PD2.Signal=GPIO_Input
PD3.Signal=GPIO_Input
PD4.Signal=GPIO_Input
PD9.Signal=GPIO_Input
PE0.Signal=GPIO_Input
PE1.Signal=GPIO_Output
PE2.Signal=GPIO_Input
PE3.Signal=GPIO_Input
PE4.Signal=GPIO_Output
PF0-OSC_IN.Mode=HSE-External-Oscillator
PF0-OSC_IN.Signal=RCC_OSC_IN
PF1-OSC_OUT.Mode=HSE-External-Oscillator
PF1-OSC_OUT.Signal=RCC_OSC_OUT
RCC.HSE_VALUE=8000000
RCC.SYSCLKFreq_VALUE=16000000
board=custom
